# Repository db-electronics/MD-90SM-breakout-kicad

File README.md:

# MD-90SM Breakout PCB
This project contains a PCB which breaks out the MD-90SM mini din 9 connector to a breadboard compatible pin header. If you're going to use my open source project you should consider sponsoring me. Thanks!

- [Github Sponsor](https://github.com/sponsors/db-electronics)
- [Pateron](https://patreon.com/dbelectronics)

# Copyright and Disclaimer
Copyright: René Richard

This documentation describes Open Hardware and is licensed under the
CERN OHL v. 1.2.

You may redistribute and modify this documentation under the terms of the
CERN OHL v.1.2. (http://ohwr.org/cernohl). This documentation is distributed
WITHOUT ANY EXPRESS OR IMPLIED WARRANTY, INCLUDING OF
MERCHANTABILITY, SATISFACTORY QUALITY AND FITNESS FOR A
PARTICULAR PURPOSE. Please see the CERN OHL v.1.2 for applicable
conditions

# BOB THERE IS NO BOM DOCUMENT THERE IS JUST ONE PART IT'S A MD-90SM I HOPE IT'S NOT CONFUSING

# EDIT FOR BOB BECAUSE HE COMPLAINED ABOUT THE PART# NOT BEING IN THE README
## THE DIGIKEY PART# IS CP-2290-ND
## TYPE THIS INTO YOUR BROWSER TO SEE IT: 
https://www.digikey.ca/products/en?keywords=md-90sm
## THIS IS WHAT IT LOOKS LIKE:

## I HOPE YOU'RE HAPPY NOW

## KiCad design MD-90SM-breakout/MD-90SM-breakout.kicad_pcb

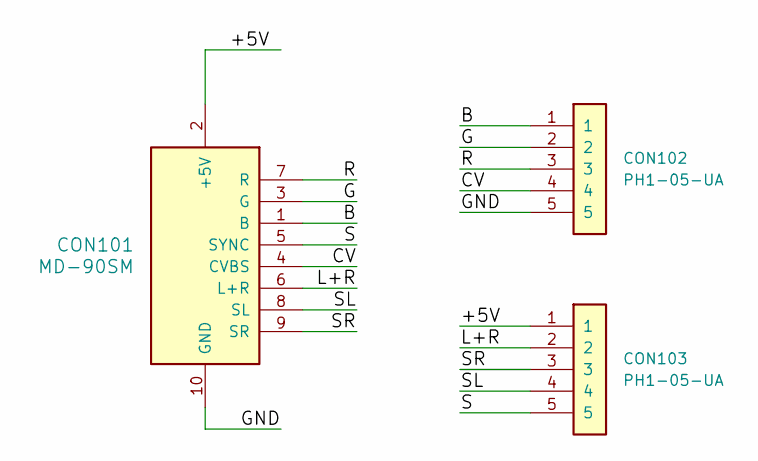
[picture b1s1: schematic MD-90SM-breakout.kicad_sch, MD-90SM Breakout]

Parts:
CON101: MD-90SM; Digikey CP-2290-ND
CON102, CON103: PH1-05-UA; HDR1X5

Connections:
/+5V: CON101.2 (+5V), CON103.1
/B: CON101.1 (B), CON102.1
/CV: CON101.4 (CVBS), CON102.4
/G: CON101.3 (G), CON102.2
/GND: CON101.10 (GND), CON102.5
/L+R: CON101.6 (L+R), CON103.2
/R: CON101.7 (R), CON102.3
/S: CON101.5 (SYNC), CON103.5
/SL: CON101.8 (SL), CON103.4
/SR: CON101.9 (SR), CON103.3

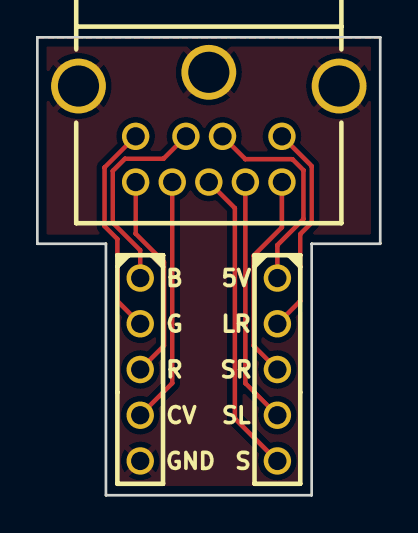
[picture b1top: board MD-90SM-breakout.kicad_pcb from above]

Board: 2 copper layers, 19.1 x 25.4 mm, 3 parts (0 on the bottom side), 10 nets.

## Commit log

2018-09-04 0.1 version release, I have no intention of testing this
2019-01-07 Update readme for RetroRGB
2024-04-07 updated to v0.2 with breadboard compatible dip spacing

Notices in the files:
MD-90SM-breakout/MD-90SM-breakout.kicad_pcb:
Licensed under CERN OHL v.1.2
